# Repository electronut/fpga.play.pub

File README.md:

## fpga.play

A low cost open source Lattice iCE40UP5k FPGA board.

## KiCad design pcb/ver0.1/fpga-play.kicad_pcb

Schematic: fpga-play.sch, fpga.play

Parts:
FID1, FID2, FID3: Fiducial; Fiducial_0.5mm_Mask1mm
H1, H2: MountingHole; MountingHole_2.2mm_M2_Pad
S1: fpga_silk; fpga_logo

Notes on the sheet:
Block Diagram

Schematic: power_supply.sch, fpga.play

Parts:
C1, C2, C3, C4, C5: 1uF; C_0603_1608Metric
D4: USBLC6-2SC6; SOT95P280X145-6N
J5: 629105136821; WE_629105136821
Q1: DMP3125L; SOT-23
R10: 1M; R_0603_1608Metric
R12: 1.5K; R_0603_1608Metric
R13, R14: 22R; R_0603_1608Metric
U1: TLV7111233DSET; SON50P150X150X80-6N
U2: MIC5501-3.0YM5-TR; SOT95P280X145-5N

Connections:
+1V2: C5.1, U1.6; also elsewhere on the board
+1V8: U2.6; also elsewhere on the board
+2V8: C4.1, U2.1; also elsewhere on the board
+3V3: C2.1, R12.1, R13.2, R14.2, U1.1; also elsewhere on the board
Flash_~WP~(PSRAM_SIO2): R14.1; also elsewhere on the board
GND: C1.2, C2.2, C3.2, C4.2, C5.2, D4.2, J5.4, J5.5, R10.2, U1.2, U2.2; also elsewhere on the board
unnamed 41: C1.1, C3.1, Q1.2, U1.3, U1.4, U1.5, U2.3, U2.4, U2.5; also elsewhere on the board
unnamed: D4.1, J5.2
unnamed: D4.3, J5.3
unnamed 47: D4.4, R12.2; also elsewhere on the board
unnamed 48: D4.6; also elsewhere on the board
unnamed: J5.S1, J5.S2, J5.S3, J5.S4, R10.1
unnamed 50: R13.1; also elsewhere on the board
VBUS: D4.5, J5.1, Q1.1; also elsewhere on the board
VCC: Q1.3; also elsewhere on the board

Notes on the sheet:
Input Voltage 2.5V to 5.5V
Power Supply
USB Bootloader

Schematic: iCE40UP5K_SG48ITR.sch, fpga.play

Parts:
C9, C11, C13, C14, C17, C21, C22: 0.1uF; C_0603_1608Metric
C10: 10uF; C_0603_1608Metric
C12, C16, C23, C24: 1uF; C_0603_1608Metric
C15, C18, C19, C20: 10nF; C_0603_1608Metric
D1: MBR130; D_SOD-123_SMD
D2: User_LED; LED_0603_1608Metric
D3: CDONE; LED_0603_1608Metric
R1: 100R; R_0603_1608Metric
R2: 2.2K; R_0603_1608Metric
R3, R5: 10K; R_0603_1608Metric
R4: 330R; R_0603_1608Metric
SW1: CRESET; SW_SPST_PTS810
SW2: User_Button; SW_SPST_PTS810
U4: SIT1602AC-12-33E-12.000000E; SOIC254P1016X440-4N
U5: ICE40UP5K-SG48ITR50; QFN50P700X700X100-49N

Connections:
+1V2: C15.1, C16.1, C17.1, R1.2, U5.5, U5.30; also elsewhere on the board
+3V3: C14.1, C21.1, C23.1, D1.2, R2.2, R3.1, R4.1, R5.1, U5.22; also elsewhere on the board
/iCE40UP5K/LED1: D2.1, U5.39
/iCE40UP5K/SW1: R5.2, SW2.1, U5.11
CDONE: D3.2, R2.1, U5.7; also elsewhere on the board
Flash_SCK(PSRAM_SCK): U5.15; also elsewhere on the board
Flash_SS: U5.16; also elsewhere on the board
Flash_~HOLD~(PSRAM_SIO3): U5.9; also elsewhere on the board
Flash_~WP~(PSRAM_SIO2): U5.10; also elsewhere on the board
GND: C9.2, C10.2, C11.2, C12.2, C13.2, C14.2, C15.2, C16.2, C17.2, C18.2, C21.2, C22.2, C23.2, C24.2, D3.1, SW1.2, SW2.2, U5.EP; also elsewhere on the board
IOB_0A: U5.46; also elsewhere on the board
IOB_2A: U5.47; also elsewhere on the board
IOB_3B_G6: U5.44; also elsewhere on the board
IOB_4A: U5.48; also elsewhere on the board
IOB_5B: U5.45; also elsewhere on the board
IOB_6A: U5.2; also elsewhere on the board
IOB_9B: U5.3; also elsewhere on the board
IOB_23B: U5.21; also elsewhere on the board
IOB_25B_G3: U5.20; also elsewhere on the board
IOB_29B: U5.19; also elsewhere on the board
IOB_31B: U5.18; also elsewhere on the board
IOT_8A: U5.4; also elsewhere on the board
IOT_13B: U5.6; also elsewhere on the board
IOT_36B: U5.25; also elsewhere on the board
IOT_37A: U5.23; also elsewhere on the board
IOT_38B: U5.27; also elsewhere on the board
IOT_39A: U5.26; also elsewhere on the board
IOT_41A: U5.28; also elsewhere on the board
IOT_42B: U5.31; also elsewhere on the board
IOT_43A: U5.32; also elsewhere on the board
IOT_44B: U5.34; also elsewhere on the board
IOT_45A_G1: U5.37; also elsewhere on the board
IOT_46B_G0: U5.35; also elsewhere on the board
IOT_48B: U5.36; also elsewhere on the board
IOT_49A: U5.43; also elsewhere on the board
IOT_50B: U5.38; also elsewhere on the board
IOT_51A: U5.42; also elsewhere on the board
unnamed: C10.1, C11.1, R1.1, U5.29
unnamed: C18.1, D1.1, U5.24
unnamed: D2.2, R4.2
RGB1: U5.40; also elsewhere on the board
RGB2: U5.41; also elsewhere on the board
USB_N: U5.13; also elsewhere on the board
USB_P: U5.12; also elsewhere on the board
VDD: C9.1, C12.1, C13.1, C22.1, C24.1, U5.1, U5.33; also elsewhere on the board
iCE_SI: U5.17; also elsewhere on the board
iCE_SO: U5.14; also elsewhere on the board
~CRESET_B: R3.2, SW1.1, U5.8; also elsewhere on the board

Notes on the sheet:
ICE40UP5K

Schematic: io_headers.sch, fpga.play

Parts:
J1, J3: IO Header; PinHeader_1x18_P2.54mm_Vertical
J2: Prog Header; PinHeader_2x05_P2.54mm_Vertical

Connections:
+3V3: J1.16, J2.4; also elsewhere on the board
CDONE: J2.6; also elsewhere on the board
Flash_MISO(PSRAM_SIO1): J2.5; also elsewhere on the board
Flash_MOSI(PSRAM_SIO0): J2.7; also elsewhere on the board
Flash_SCK(PSRAM_SCK): J2.3; also elsewhere on the board
Flash_SS: J2.1; also elsewhere on the board
Flash_~HOLD~(PSRAM_SIO3): J2.9; also elsewhere on the board
Flash_~WP~(PSRAM_SIO2): J2.10; also elsewhere on the board
GND: J1.15, J2.2, J3.15; also elsewhere on the board
IOB_0A: J3.3; also elsewhere on the board
IOB_2A: J3.2; also elsewhere on the board
IOB_3B_G6: J3.5; also elsewhere on the board
IOB_4A: J3.1; also elsewhere on the board
IOB_5B: J3.4; also elsewhere on the board
IOB_6A: J1.1; also elsewhere on the board
IOB_9B: J1.2; also elsewhere on the board
IOB_23B: J1.14; also elsewhere on the board
IOB_25B_G3: J1.13; also elsewhere on the board
IOB_29B: J1.12; also elsewhere on the board
IOB_31B: J1.11; also elsewhere on the board
IOT_8A: J1.3; also elsewhere on the board
IOT_36B: J1.5; also elsewhere on the board
IOT_37A: J1.4; also elsewhere on the board
IOT_38B: J1.7; also elsewhere on the board
IOT_39A: J1.6; also elsewhere on the board
IOT_41A: J1.8; also elsewhere on the board
IOT_42B: J1.9; also elsewhere on the board
IOT_43A: J1.10; also elsewhere on the board
IOT_44B: J3.14; also elsewhere on the board
IOT_45A_G1: J3.11; also elsewhere on the board
IOT_46B_G0: J3.13; also elsewhere on the board
IOT_48B: J3.12; also elsewhere on the board
IOT_49A: J3.6; also elsewhere on the board
IOT_50B: J3.10; also elsewhere on the board
IOT_51A: J3.7; also elsewhere on the board
RGB1: J3.9; also elsewhere on the board
RGB2: J3.8; also elsewhere on the board
VCC: J3.16; also elsewhere on the board
~CRESET_B: J2.8; also elsewhere on the board

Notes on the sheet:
GPIO Header
Programming Header

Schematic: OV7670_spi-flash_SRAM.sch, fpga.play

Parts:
C25, C26, C29: 0.1uF; C_0603_1608Metric
JP1, JP2, JP3: SolderJumper_2_Bridged; R_0402_1005Metric
R6, R7, R8, R9, R11, R15, R16: 10K; R_0603_1608Metric
U6: W25Q32JVSSIQ; SOIC-8_5.23x5.23mm_P1.27mm
U7: APS6404L; SOIC-8_3.9x4.9mm_P1.27mm

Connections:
+3V3: C25.1, C26.1, R6.2, R11.2, U6.8 (VCC), U7.8 (VCC); also elsewhere on the board
Flash_MISO(PSRAM_SIO1): JP3.2, U6.2 (DO(IO1)), U7.2 (SO/SIO(1)); also elsewhere on the board
Flash_MOSI(PSRAM_SIO0): JP2.1, U6.5 (DI(IO0)), U7.5 (SI/SIO(0)); also elsewhere on the board
Flash_SCK(PSRAM_SCK): R11.1, U6.6 (CLK), U7.6 (SCLK); also elsewhere on the board
Flash_SS: JP1.2; also elsewhere on the board
Flash_~HOLD~(PSRAM_SIO3): U6.7 (~HOLD/!RST(IO3)~), U7.7 (SIO(3)); also elsewhere on the board
Flash_~WP~(PSRAM_SIO2): U6.3 (~WP(IO2)~), U7.3 (SIO(2)); also elsewhere on the board
GND: C25.2, C26.2, C29.2, R7.2, U6.4 (GND), U7.4 (VSS); also elsewhere on the board
IOB_0A: R16.1; also elsewhere on the board
IOT_49A: R15.1; also elsewhere on the board
unnamed 47: R9.2; also elsewhere on the board
unnamed 48: R8.2; also elsewhere on the board
unnamed 50: JP1.1, U6.1 (~CS~); also elsewhere on the board
unnamed 51: R6.1, U7.1 (~CE); also elsewhere on the board
USB_N: R8.1; also elsewhere on the board
USB_P: R9.1; also elsewhere on the board
VBUS: R7.1; also elsewhere on the board
VDD: C29.1, R15.2, R16.2; also elsewhere on the board
iCE_SI: JP3.1; also elsewhere on the board
iCE_SO: JP2.2; also elsewhere on the board

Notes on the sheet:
PSRAM
24 Pin FPC Connector
Flash Memory
For programming FPGA RAM
For programming Flash
For programming FPGA RAM directly cut the 1-2 traces from JP2 and JP3 and connect them as 1-1 and 2-2.
JP1: Cut the 1-2 trace for programming FPGA RAM

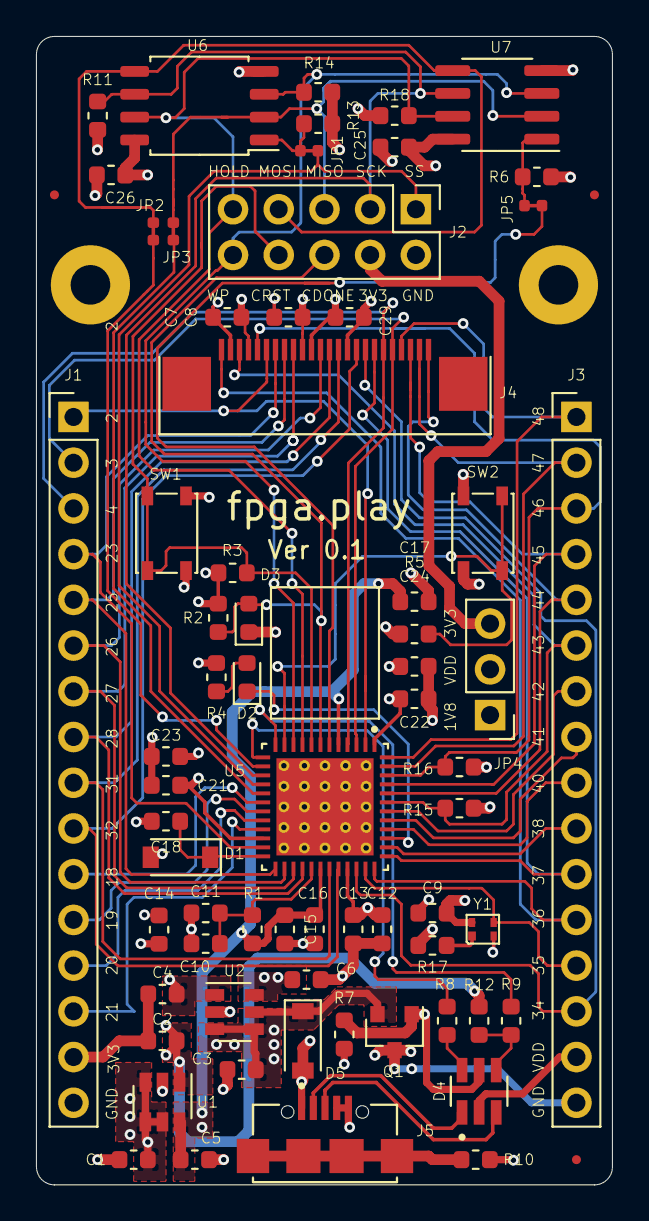
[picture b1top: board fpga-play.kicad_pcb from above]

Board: 4 copper layers, 32.0 x 63.8 mm, 74 parts (1 on the bottom side), 63 nets.

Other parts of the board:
C6: 1uF; C_0603_1608Metric
C7, C8: 0.1uF; C_0603_1608Metric
D5: MBR120; D_SOD-123
G1: logo; EL_logo
J4: OV_2640; 68712414522
JP4: Jumper_3_Bridged12; PinHeader_1x03_P2.54mm_Vertical
JP5: SolderJumper_2_Bridged; shorting_jumper-0402
R17, R18: 10K; R_0603_1608Metric
Y1: DSC6101CI1A-012.0000T; DSC6101CI1A-012_0000T

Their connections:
+1V8: C6.1, JP4.1; also elsewhere on the board
+2V8: C7.1, C8.1, J4.4, J4.10; also elsewhere on the board
+3V3: JP4.3, R18.2; also elsewhere on the board
Flash_~HOLD~(PSRAM_SIO3): R18.1; also elsewhere on the board
GND: C6.2, C7.2, C8.2, J4.2, J4.15, Y1.2; also elsewhere on the board
IOB_0A: J4.5; also elsewhere on the board
IOB_2A: J4.23; also elsewhere on the board
IOB_3B_G6: J4.24; also elsewhere on the board
IOB_4A: J4.21; also elsewhere on the board
IOB_5B: J4.22; also elsewhere on the board
IOB_6A: J4.6; also elsewhere on the board
IOB_9B: J4.20; also elsewhere on the board
IOT_8A: J4.19; also elsewhere on the board
IOT_13B: JP5.2; also elsewhere on the board
IOT_36B: J4.8; also elsewhere on the board
IOT_37A: J4.7; also elsewhere on the board
IOT_38B: J4.9; also elsewhere on the board
IOT_39A: J4.12; also elsewhere on the board
IOT_41A: J4.13; also elsewhere on the board
IOT_42B: J4.14; also elsewhere on the board
IOT_43A: J4.16; also elsewhere on the board
IOT_44B: J4.17; also elsewhere on the board
IOT_45A_G1: J4.18; also elsewhere on the board
IOT_46B_G0: Y1.3; also elsewhere on the board
IOT_48B: J4.1; also elsewhere on the board
IOT_49A: J4.3; also elsewhere on the board
unnamed 41: D5.1; also elsewhere on the board
unnamed 51: JP5.1; also elsewhere on the board
unnamed: R17.2, Y1.1
VBUS: D5.2; also elsewhere on the board
VDD: J4.11, JP4.2, R17.1, Y1.4; also elsewhere on the board

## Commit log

2020-07-12 added schematic
2020-08-03 design files added
2020-08-03 removed unwanted files
2020-08-03 layout rendor added
2020-08-03 render files updated
2020-08-03 updated image
2020-12-14 schematic changes updated
2020-12-15 library files added
